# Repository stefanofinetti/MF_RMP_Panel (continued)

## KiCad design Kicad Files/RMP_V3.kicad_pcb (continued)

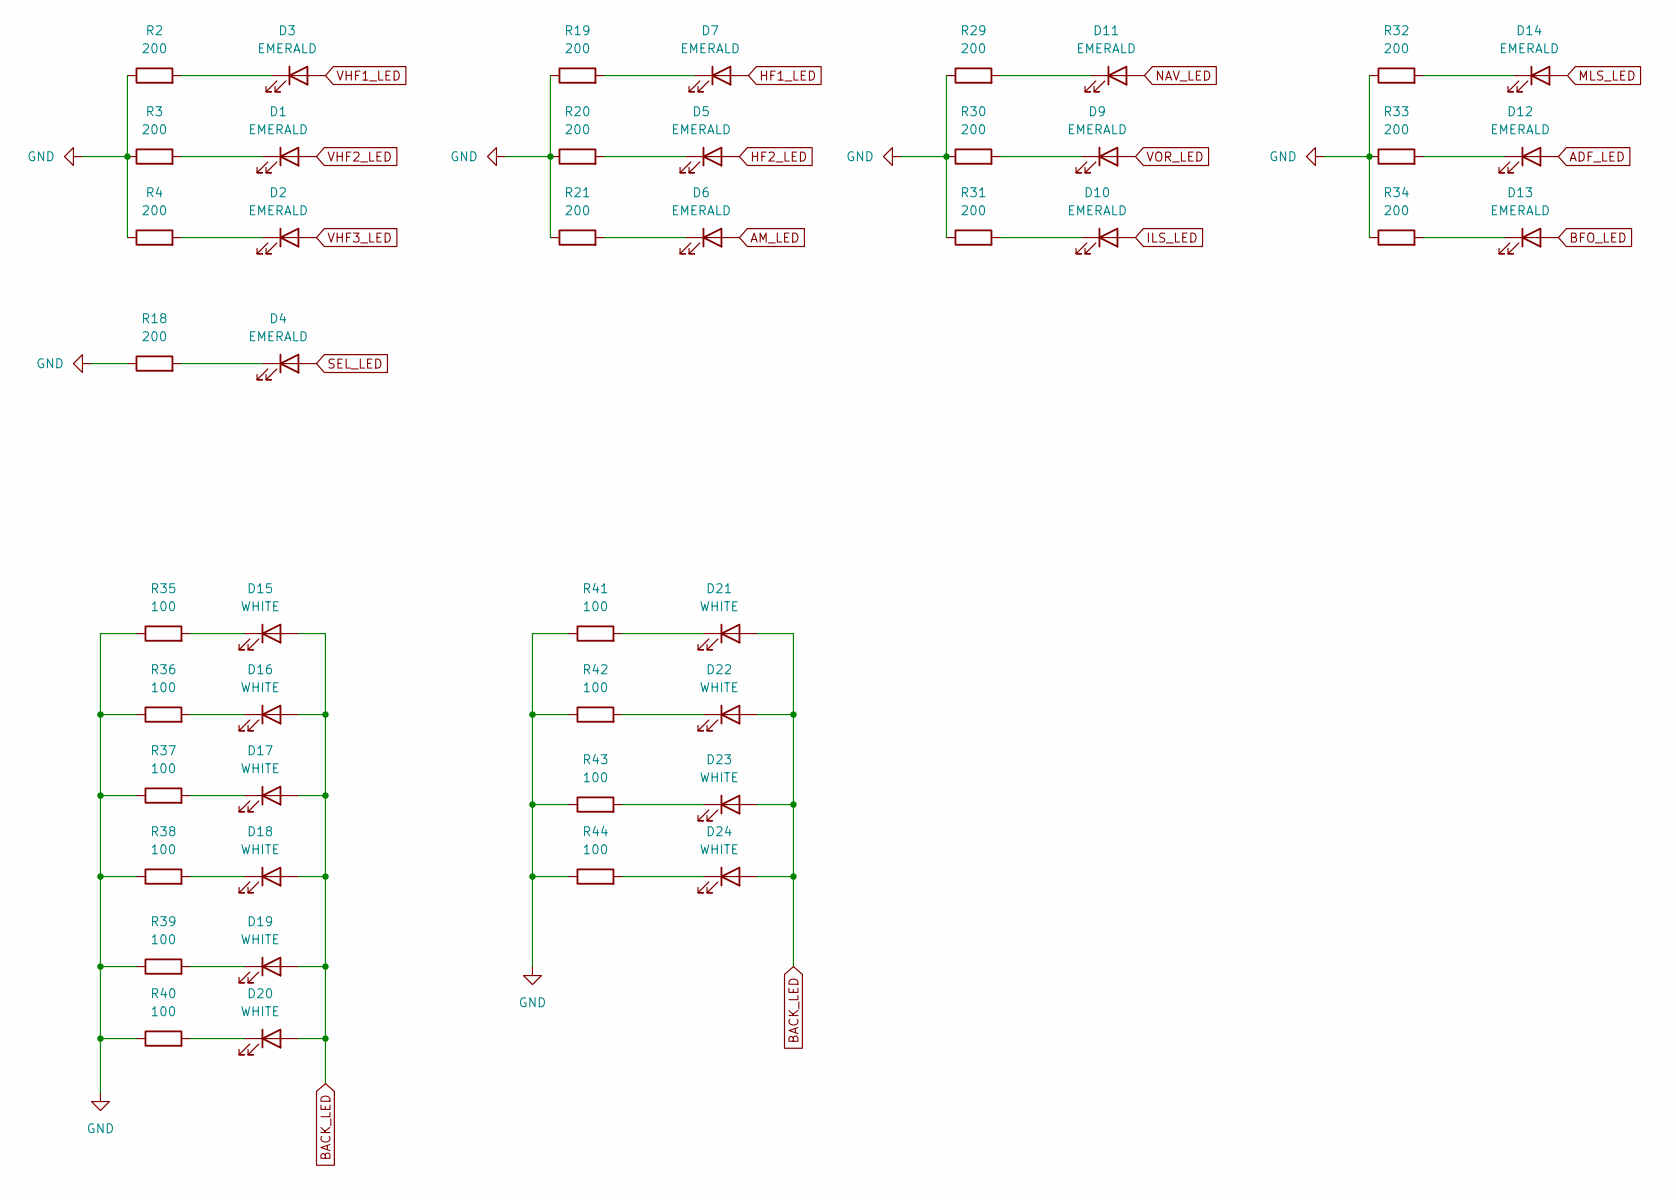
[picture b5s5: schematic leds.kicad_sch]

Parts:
D1, D2, D3, D4, D5, D6, D7, D9, D10, D11, D12, D13, D14: EMERALD; LED_D3.0mm_FlatTop
D15, D16, D17, D18, D19, D20, D21, D22, D23, D24: WHITE; LED_1206_3216Metric_Pad1.42x1.75mm_HandSolder
R2, R3, R4, R18, R19, R20, R21, R29, R30, R31, R32, R33, R34: 200; R_1206_3216Metric_Pad1.30x1.75mm_HandSolder
R35, R36, R37, R38, R39, R40, R41, R42, R43, R44: 100; R_1206_3216Metric_Pad1.30x1.75mm_HandSolder

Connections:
ADF_LED: D12.2 (A); also elsewhere on the board
AM_LED: D6.2 (A); also elsewhere on the board
BACK_LED: D15.2 (A), D16.2 (A), D17.2 (A), D18.2 (A), D19.2 (A), D20.2 (A), D21.2 (A), D22.2 (A), D23.2 (A), D24.2 (A); also elsewhere on the board
BFO_LED: D13.2 (A); also elsewhere on the board
GND: R2.1, R3.1, R4.1, R18.1, R19.1, R20.1, R21.1, R29.1, R30.1, R31.1, R32.1, R33.1, R34.1, R35.1, R36.1, R37.1, R38.1, R39.1, R40.1, R41.1, R42.1, R43.1, R44.1; also elsewhere on the board
HF1_LED: D7.2 (A); also elsewhere on the board
HF2_LED: D5.2 (A); also elsewhere on the board
ILS_LED: D10.2 (A); also elsewhere on the board
MLS_LED: D14.2 (A); also elsewhere on the board
NAV_LED: D11.2 (A); also elsewhere on the board
unnamed: D1.1 (K), R3.2
unnamed: D2.1 (K), R4.2
unnamed: D3.1 (K), R2.2
unnamed: D4.1 (K), R18.2
unnamed: D5.1 (K), R20.2
unnamed: D6.1 (K), R21.2
unnamed: D7.1 (K), R19.2
unnamed: D9.1 (K), R30.2
unnamed: D10.1 (K), R31.2
unnamed: D11.1 (K), R29.2
unnamed: D12.1 (K), R33.2
unnamed: D13.1 (K), R34.2
unnamed: D14.1 (K), R32.2
unnamed: D15.1 (K), R35.2
unnamed: D16.1 (K), R36.2
unnamed: D17.1 (K), R37.2
unnamed: D18.1 (K), R38.2
unnamed: D19.1 (K), R39.2
unnamed: D20.1 (K), R40.2
unnamed: D21.1 (K), R41.2
unnamed: D22.1 (K), R42.2
unnamed: D23.1 (K), R43.2
unnamed: D24.1 (K), R44.2
SEL_LED: D4.2 (A); also elsewhere on the board
VHF1_LED: D3.2 (A); also elsewhere on the board
VHF2_LED: D1.2 (A); also elsewhere on the board
VHF3_LED: D2.2 (A); also elsewhere on the board
VOR_LED: D9.2 (A); also elsewhere on the board

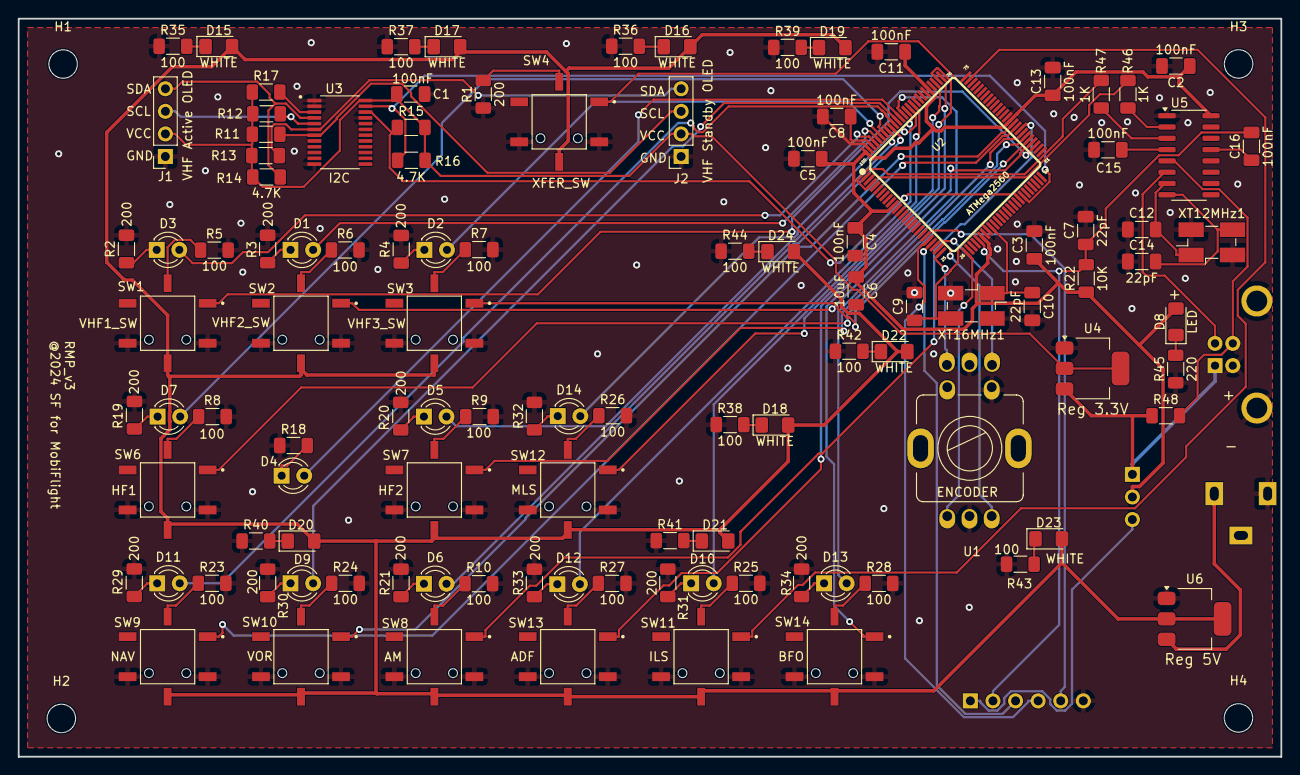
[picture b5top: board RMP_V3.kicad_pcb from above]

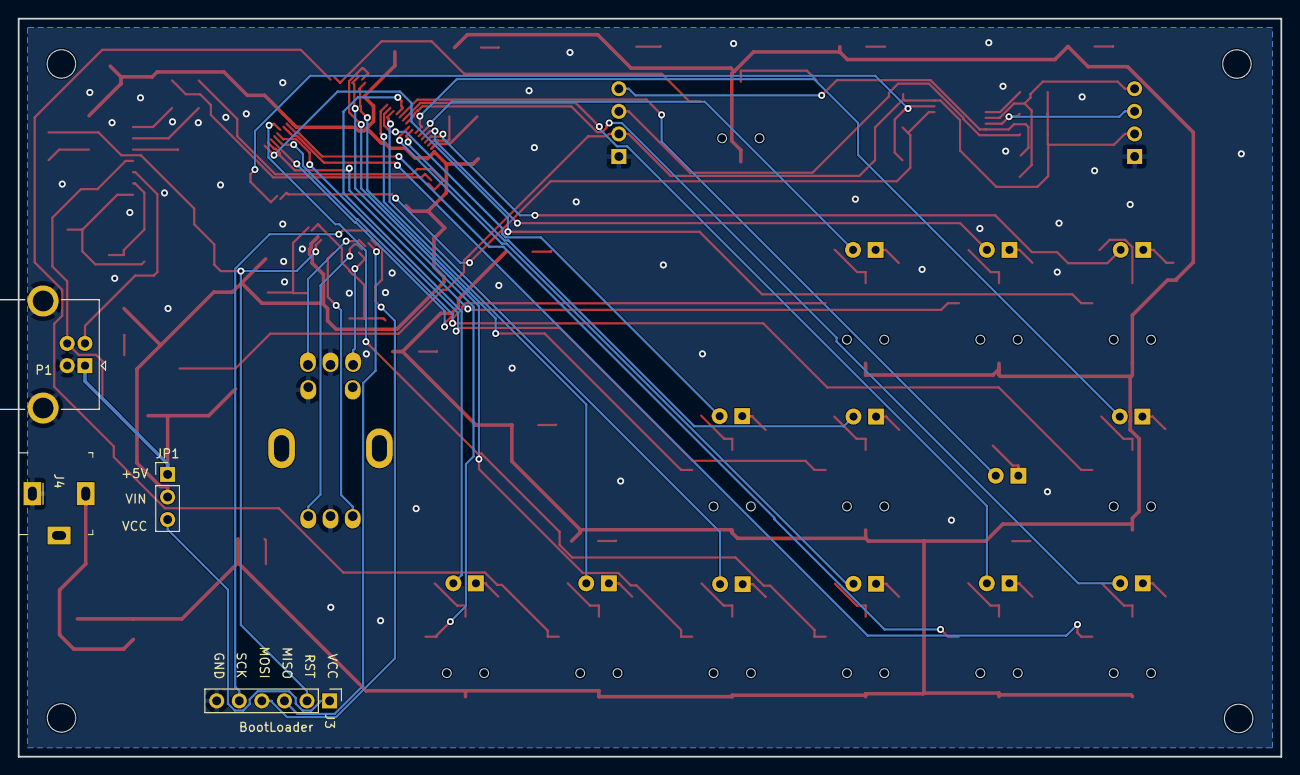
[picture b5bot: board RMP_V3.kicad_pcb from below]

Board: 2 copper layers, 142.0 x 83.0 mm, 119 parts (4 on the bottom side), 98 nets.

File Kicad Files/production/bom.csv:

Designator,Footprint,Quantity,Value,LCSC Part #
"C1, C11, C13, C15, C16, C2, C3, C4, C5, C8",1206,10,100nF,
"C10, C12, C14, C7, C9",1206,5,22pF,
C6,1206,1,10uF,
"D1, D10, D11, D12, D13, D14, D2, D3, D4, D5, D6, D7, D9",LED_D3.0mm_FlatTop,13,EMERALD,
"D15, D16, D17, D18, D19, D20, D21, D22, D23, D24",1206,10,WHITE,
D8,1206,1,LED,
J1,PinSocket_1x04_P2.54mm_Vertical,1,VHF Active OLED,
J2,PinSocket_1x04_P2.54mm_Vertical,1,VHF Standby OLED,
J3,PinHeader_1x06_P2.54mm_Vertical,1,BootLoader,
J4,Barrel_Jack_5.5mmODx2.1mmID_PJ-102A,1,PJ-102A,PJ-102A
JP1,PinHeader_1x03_P2.54mm_Vertical,1,Power Selector,
P1,USB_B_OST_USB-B1HSxx_Horizontal,1,USB_C_Plug_USB2.0,
"R1, R18, R19, R2, R20, R21, R29, R3, R30, R31, R32, R33, R34, R4",1206,14,200,
"R10, R23, R24, R25, R26, R27, R28, R35, R36, R37, R38, R39, R40, R41, R42, R43, R44, R5, R6, R7, R8, R9",1206,22,100,
"R11, R12, R13, R14, R15, R16",1206,6,4.7K,
"R17, R22",1206,2,10K,
R45,1206,1,220,
"R46, R47",1206,2,1K,
R48,1206,1,1.5K,
SW1,SW_TL3240F260R,1,VHF1_SW,C4364809
SW10,SW_TL3240F260R,1,VOR,C4364985
SW11,SW_TL3240F260R,1,ILS,C4364985
SW12,SW_TL3240F260R,1,MLS,C4364985
SW13,SW_TL3240F260R,1,ADF,C4364985
SW14,SW_TL3240F260R,1,BFO,C4364985
SW2,SW_TL3240F260R,1,VHF2_SW,C4364809
SW3,SW_TL3240F260R,1,VHF3_SW,C4364809
SW4,SW_TL3240F260R,1,XFER_SW,C4364985
SW6,SW_TL3240F260R,1,HF1,C4364809
SW7,SW_TL3240F260R,1,HF2,C4364809
SW8,SW_TL3240F260R,1,AM,C4364809
SW9,SW_TL3240F260R,1,NAV,C4364985
U1,EC11EBB24C03,1,ENCODER,
U2,TQFP100-0.5-14X14MM,1,ATMega2560,
U3,SOP65P640X120-24N,1,PCA9548APW,
U4,SOT-223-3_TabPin2,1,AMS1117-3.3,
U5,SOIC-16_3.9x9.9mm_P1.27mm,1,CH340G,
U6,SOT-223-3_TabPin2,1,AMS1117-5.0,
XT12MHZ1,Crystal_SMD_EuroQuartz_MJ-4Pin_5.0x3.2mm_HandSoldering,1,12MHz,
XT16MHZ1,Crystal_SMD_EuroQuartz_MJ-4Pin_5.0x3.2mm_HandSoldering,1,16MHz,

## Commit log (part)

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2024-12-17 First Commit of the RMP Project
2024-12-17 Commit of LICENSE and README in the RMP Project
2025-03-08 Various updates and fixes
